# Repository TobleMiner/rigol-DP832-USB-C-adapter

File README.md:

Rigol DP832 USB-C adapter
=========================

This PCB is a dual USB-C port adapter for the Rigol DP832.  
Slotting right onto channel three of the DP832 it provides you with dual
USB-C ports for powering your homemade USB gadgets.

**Note this design is still untested. PCBs are on their way from China but will take
some more weeks**

# Limitations

This board is 5V only. No PD negotiation supported.

# Ordering

The fabrication files inside `fab` are JLCPCB-ready. Leave settings at default but select
ENIG surface finish and specify order number location for best results. Also remember to
choose your favourite PCB color ;)  

The zip archive does also contain all files required for JLC assembly. So you can also order
fully assembled boards from JLC.

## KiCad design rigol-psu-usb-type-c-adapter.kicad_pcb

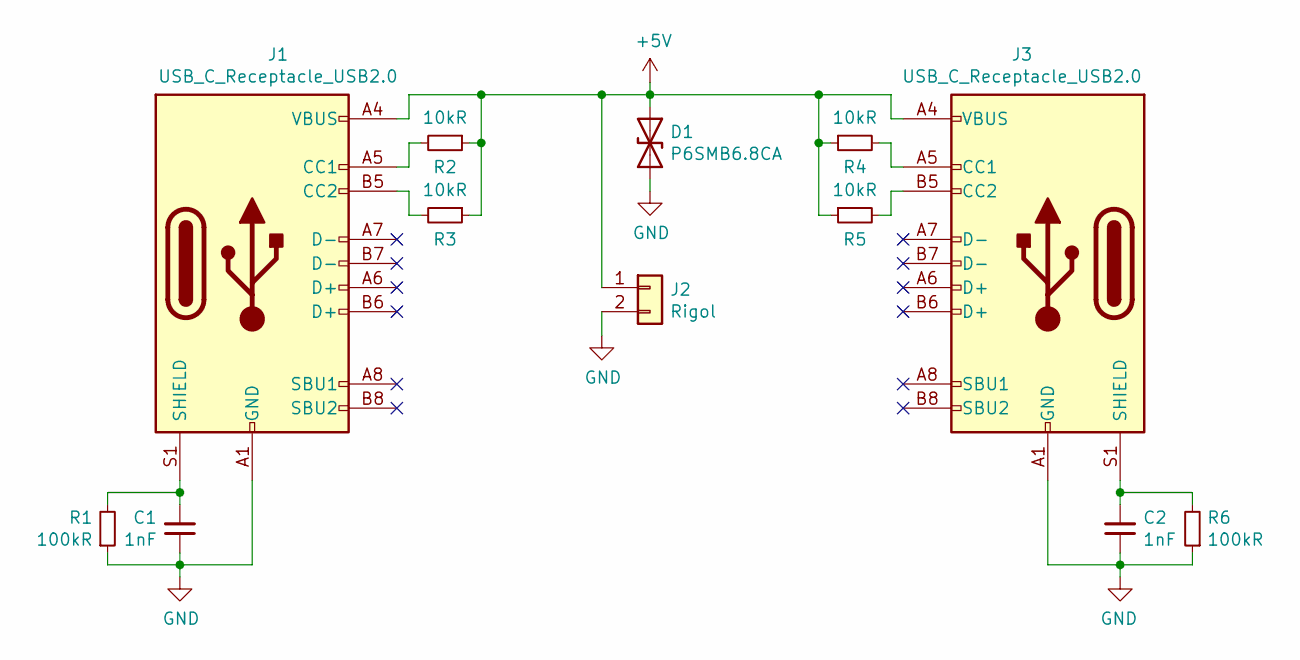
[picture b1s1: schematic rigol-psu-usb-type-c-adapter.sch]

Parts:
C1, C2: 1nF; C_1206_3216Metric; LCSC C35216
D1: P6SMB6.8CA; D_SMB; LCSC C78395
J1, J3: USB_C_Receptacle_USB2.0; USB_C_Receptacle_Palconn_UTC16-G; LCSC C167321
J2: Rigol; DP832
R1, R6: 100kR; R_1206_3216Metric; LCSC C17900
R2, R3, R4, R5: 10kR; R_0402_1005Metric; LCSC C25744

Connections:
+5V: D1.1 (A1), J1.A4 (VBUS), J1.A9 (VBUS), J1.B4 (VBUS), J1.B9 (VBUS), J2.1, J3.A4 (VBUS), J3.A9 (VBUS), J3.B4 (VBUS), J3.B9 (VBUS), R2.1, R3.1, R4.1, R5.1
GND: C1.1, C2.1, D1.2 (A2), J1.A1 (GND), J1.A12 (GND), J1.B1 (GND), J1.B12 (GND), J2.2, J3.A1 (GND), J3.A12 (GND), J3.B1 (GND), J3.B12 (GND), R1.1, R6.1
unnamed: C1.2, J1.S1 (SHIELD), R1.2
unnamed: C2.2, J3.S1 (SHIELD), R6.2
unnamed: J1.A5 (CC1), R2.2
unnamed: J1.B5 (CC2), R3.2
unnamed: J3.A5 (CC1), R4.2
unnamed: J3.B5 (CC2), R5.2

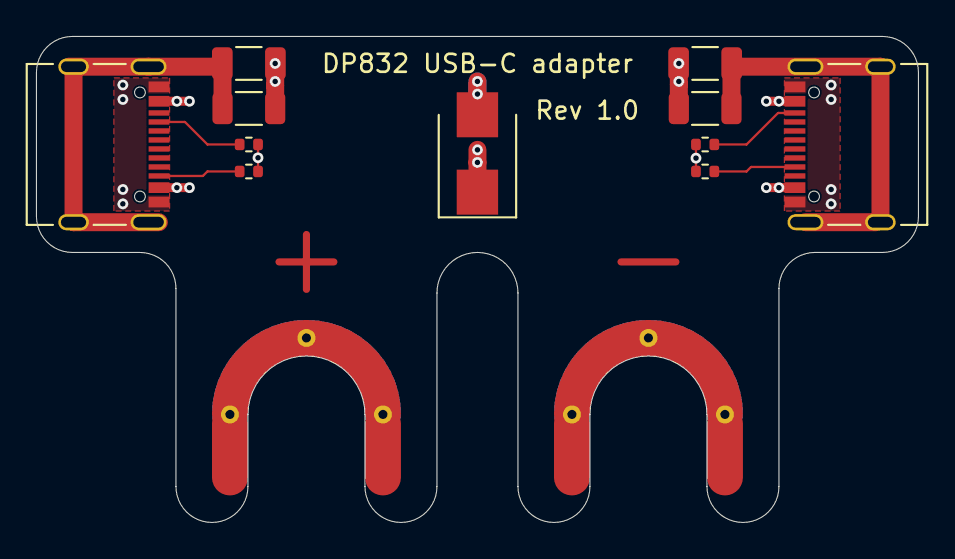
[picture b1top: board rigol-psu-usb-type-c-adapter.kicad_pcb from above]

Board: 2 copper layers, 49.0 x 27.0 mm, 12 parts (0 on the bottom side), 8 nets.

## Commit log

2021-06-29 Fix typo
2021-06-29 Extend readme
2021-06-29 Fix CC pull-ups
    Memory fooled me. They need to be 10kR, not 5.1kR.
2021-06-29 Add schematic export
2021-06-29 Add license
2021-06-29 Add kitspace.yaml
2021-06-29 Add assembly files
2021-06-29 Fix CC resistor part number
2021-06-29 Sync fabrication files
